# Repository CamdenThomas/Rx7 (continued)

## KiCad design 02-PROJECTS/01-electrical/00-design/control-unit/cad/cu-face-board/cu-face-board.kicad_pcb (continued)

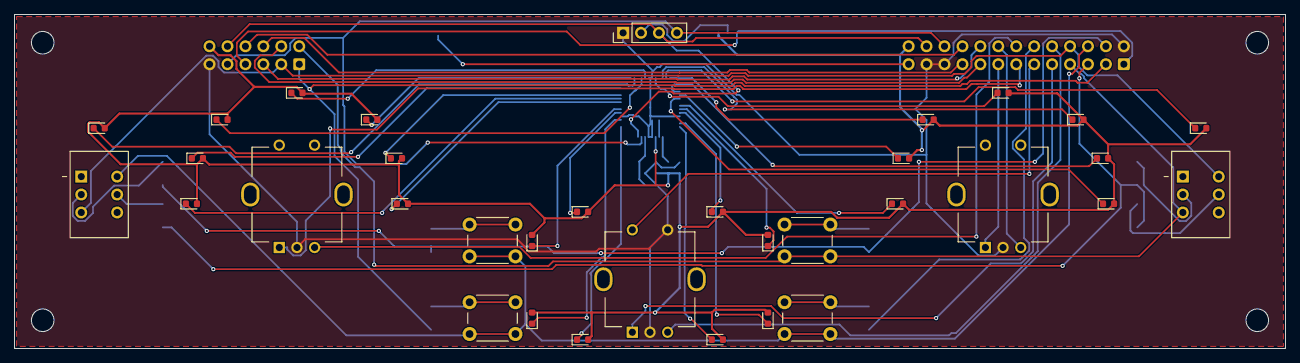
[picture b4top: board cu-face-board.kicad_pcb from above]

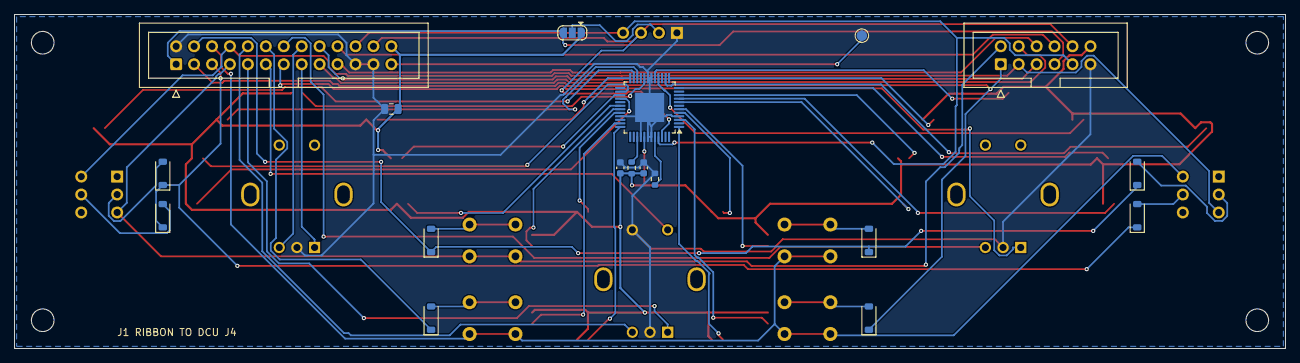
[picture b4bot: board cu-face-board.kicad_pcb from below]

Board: 2 copper layers, 180.0 x 47.3 mm, 56 parts (18 on the bottom side), 59 nets.

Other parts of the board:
H1, H2, H3, H4: M3; MountingHole_3.2mm_M3

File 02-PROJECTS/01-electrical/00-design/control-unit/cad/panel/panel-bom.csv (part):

"Ref","Qty","Value","Footprint","DNP","Confirm"
"C1","1","10uF 16V X7R","Capacitor_SMD:C_0805_2012Metric","","at J1 pin 26, for the LEDs' PWM current - part number confirm (P192)"
"C2","1","1uF","Capacitor_SMD:C_0603_1608Metric","","at U2 VCC - part number confirm (P192)"
"C3","1","100nF","Capacitor_SMD:C_0603_1608Metric","","at U2 VCC - part number confirm (P192)"
"D1-D8","8","1N4148W","Diode_SMD:D_SOD-123","",""
"J1","1","panel ribbon 2x13 IDC, keyed","Connector_IDC:IDC-Header_2x13_P2.54mm_Vertical","","keyed shrouded box header, the part bought confirm (P157); pin 1 toward the board's right edge"
"J2","1","screen module I2C 4-pin","Connector_PinHeader_2.54mm:PinHeader_1x04_P2.54mm_Vertical","","placeholder for the module's header (P201 not picked): pin order GND VCC SCL SDA and the standoff that brings the glass to the faceplate window - confirm"
"J3","1","plate header 2x6 IDC, keyed (DP-DCU-E 1-12)","Connector_IDC:IDC-Header_2x06_P2.54mm_Vertical","","the lead to the upper board's J8 (P196 class), pin n = DP-DCU-E n - confirm"
"LED1","1","key light rear defog","LED_SMD:LED_0603_1608Metric","","0603; colour per LP20 (P192), brightness on the bench - confirm. under the rear-defog cap (state, any time, I-004)"
"LED2","1","key light HVAC mode","LED_SMD:LED_0603_1608Metric","","0603; colour per LP20 (P192), brightness on the bench - confirm. under the fan-mode cap"
"LED3","1","key light recirculate","LED_SMD:LED_0603_1608Metric","","0603; colour per LP20 (P192), brightness on the bench - confirm. under the recirculate cap; green when on (I-001)"
"LED4","1","key light mirror defog","LED_SMD:LED_0603_1608Metric","","0603; colour per LP20 (P192), brightness on the bench - confirm. under the mirror-defog cap"
"LED5","1","knob ring 1","LED_SMD:LED_0603_1608Metric","","0603; colour per LP20 (P192), brightness on the bench - confirm. centre knob's ring, upper left (headlights only, I-004)"
"LED6","1","knob ring 2","LED_SMD:LED_0603_1608Metric","","0603; colour per LP20 (P192), brightness on the bench - confirm. centre knob's ring, upper right"
"LED7","1","knob ring 3","LED_SMD:LED_0603_1608Metric","","0603; colour per LP20 (P192), brightness on the bench - confirm. centre knob's ring, lower right"
"LED8","1","knob ring 4","LED_SMD:LED_0603_1608Metric","","0603; colour per LP20 (P192), brightness on the bench - confirm. centre knob's ring, lower left"
"LED9","1","window symbol DRV","LED_SMD:LED_0603_1608Metric","","0603; colour per LP20 (P192), brightness on the bench - confirm. beside the DRV window switch; a lit cap on the switch is a part question (I-005)"
"LED10","1","window symbol PASS","LED_SMD:LED_0603_1608Metric","","0603; colour per LP20 (P192), brightness on the bench - confirm. beside the PASS window switch (I-005)"
"LED11","1","seat symbol DRV","LED_SMD:LED_0603_1608Metric","","0603; colour per LP20 (P192), brightness on the bench - confirm. beside the driver seat knob: a fixed lit centre needs a hollow-shaft encoder, not chosen (I-005)"
"LED12","1","seat symbol PASS","LED_SMD:LED_0603_1608Metric","","0603; colour per LP20 (P192), brightness on the bench - confirm. beside the passenger seat knob (I-005)"
"LED13","1","driver seat cool 3","LED_SMD:LED_0603_1608Metric","","0603; colour per LP20 (P192), brightness on the bench - confirm. blue - driver seat arc, anticlockwise of OFF (D-073)"
"LED14","1","driver seat cool 2","LED_SMD:LED_0603_1608Metric","","0603; colour per LP20 (P192), brightness on the bench - confirm. blue"
"LED15","1","driver seat cool 1","LED_SMD:LED_0603_1608Metric","","0603; colour per LP20 (P192), brightness on the bench - confirm. blue"
"LED16","1","driver seat heat 1","LED_SMD:LED_0603_1608Metric","","0603; colour per LP20 (P192), brightness on the bench - confirm. red - clockwise of OFF"
"LED17","1","driver seat heat 2","LED_SMD:LED_0603_1608Metric","","0603; colour per LP20 (P192), brightness on the bench - confirm. red"
"LED18","1","driver seat heat 3","LED_SMD:LED_0603_1608Metric","","0603; colour per LP20 (P192), brightness on the bench - confirm. red"
"LED19","1","passenger seat cool 3","LED_SMD:LED_0603_1608Metric","","0603; colour per LP20 (P192), brightness on the bench - confirm. blue - passenger seat arc"
"LED20","1","passenger seat cool 2","LED_SMD:LED_0603_1608Metric","","0603; colour per LP20 (P192), brightness on the bench - confirm. blue"
"LED21","1","passenger seat cool 1","LED_SMD:LED_0603_1608Metric","","0603; colour per LP20 (P192), brightness on the bench - confirm. blue"
"LED22","1","passenger seat heat 1","LED_SMD:LED_0603_1608Metric","","0603; colour per LP20 (P192), brightness on the bench - confirm. red"
"LED23","1","passenger seat heat 2","LED_SMD:LED_0603_1608Metric","","0603; colour per LP20 (P192), brightness on the bench - confirm. red"
"LED24","1","passenger seat heat 3","LED_SMD:LED_0603_1608Metric","","0603; colour per LP20 (P192), brightness on the bench - confirm. red"
"R1","1","10k","Resistor_SMD:R_0603_1608Metric","","IMAX 7.6 mA per channel (p.11) - part number confirm (P192)"
"R2","1","100k","Resistor_SMD:R_0603_1608Metric","","SDB held high: on and blank until written - part number confirm (P192)"
"SW1","1","key - rear defog","Button_Switch_THT:SW_PUSH_6mm_H13mm","","Same Sky TS02-66-130-BK-160-LCR-D (P155, luxury D-488): 6 x 6 mm THT tactile, its top 13.0 mm above the board, 160 gf. The footprint is the maker's drawing rev 1.03: 6.5 x 4.5 mm, four 1.0 mm holes, pins 1-2 and 3-4 joined. The mock-up puts the cap's front 13 mm from the board (8 + 3 + 2): the cap's own top adds to that, or the 12.0 mm TS02-66-120-BK-160-LCR-D leaves it 1 mm - confirm with the cap (LP20)"
"SW2","1","key - HVAC mode","Button_Switch_THT:SW_PUSH_6mm_H13mm","","Same Sky TS02-66-130-BK-160-LCR-D (P155, luxury D-488): 6 x 6 mm THT tactile, its top 13.0 mm above the board, 160 gf. The footprint is the maker's drawing rev 1.03: 6.5 x 4.5 mm, four 1.0 mm holes, pins 1-2 and 3-4 joined. The mock-up puts the cap's front 13 mm from the board (8 + 3 + 2): the cap's own top adds to that, or the 12.0 mm TS02-66-120-BK-160-LCR-D leaves it 1 mm - confirm with the cap (LP20)"
"SW3","1","key - recirculate","Button_Switch_THT:SW_PUSH_6mm_H13mm","","Same Sky TS02-66-130-BK-160-LCR-D (P155, luxury D-488): 6 x 6 mm THT tactile, its top 13.0 mm above the board, 160 gf. The footprint is the maker's drawing rev 1.03: 6.5 x 4.5 mm, four 1.0 mm holes, pins 1-2 and 3-4 joined. The mock-up puts the cap's front 13 mm from the board (8 + 3 + 2): the cap's own top adds to that, or the 12.0 mm TS02-66-120-BK-160-LCR-D leaves it 1 mm - confirm with the cap (LP20)"
"SW4","1","key - mirror defog","Button_Switch_THT:SW_PUSH_6mm_H13mm","","Same Sky TS02-66-130-BK-160-LCR-D (P155, luxury D-488): 6 x 6 mm THT tactile, its top 13.0 mm above the board, 160 gf. The footprint is the maker's drawing rev 1.03: 6.5 x 4.5 mm, four 1.0 mm holes, pins 1-2 and 3-4 joined. The mock-up puts the cap's front 13 mm from the board (8 + 3 + 2): the cap's own top adds to that, or the 12.0 mm TS02-66-120-BK-160-LCR-D leaves it 1 mm - confirm with the cap (LP20)"
"SW5","1","window DRV","panel:Toggle_DPDT_SubMini_2x3_P2.54mm","","sub-miniature centre-sprung (ON)-OFF-(ON) DPDT toggle, 2 x 3 PC pins on 2.54 x 5.08 mm - part and pinout confirm (P155); lit cap for the window symbol is a part question (I-005)"
"SW6","1","window PASS","panel:Toggle_DPDT_SubMini_2x3_P2.54mm","","sub-miniature centre-sprung (ON)-OFF-(ON) DPDT toggle, 2 x 3 PC pins on 2.54 x 5.08 mm - part and pinout confirm (P155); lit cap for the window symbol is a part question (I-005)"
"SW7","1","encoder - centre","panel:RotaryEncoder_Bourns_Vertical_PEC11R-4xxxF-Sxxxx","","PEC11R-4220F-S0024 class (P155): detents, push, 20 mm shaft - confirm"
"SW8","1","encoder - driver seat","panel:RotaryEncoder_Bourns_Vertical_PEC11R-4xxxF-Sxxxx","","PEC11R-4220F-N0024 class (P155): detents, no push - confirm; the lit seat symbol in the knob's centre needs a hollow-shaft part (I-005), not chosen"
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
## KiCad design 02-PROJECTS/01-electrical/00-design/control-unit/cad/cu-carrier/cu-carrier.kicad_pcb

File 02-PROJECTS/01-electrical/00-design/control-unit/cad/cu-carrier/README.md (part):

# DCU carrier — the KiCad project

> **OUTDATED by the overhaul (D-612).** This is the last drawn state from before the boxes: the CU's connector is the DRC 64 with a DTP comfort inlet (D-594, D-612), the seats' heat and cool are its + side switches and the radar receiver is inside it (D-597), the face is the eighth pass (D-602), the CUR is on four I2C wires (D-604). It is kept as it is until row Y70 redraws it; the brief is `00-design/diagrams/overhaul-plan.html`, and the record (`../data/`) is what it must match.

*Rev 2026-10-13 (sheet rev 0.07 - Y44's fix pass, D-549, values only; rev 0.06 was Y44's one value, 0.05 Y42, 0.04 D-458, D-465, Y12) · owns: what this KiCad project
is for, what it may claim, and how to start. The board's design is `../../../../data/dcu_channels.csv`.
That is the record, and this is a drawing of it. Read `../../../README.md` first: it is the fence.*

> **Y49 / D-593 (2026-10-14): the dash-light stage is on the sheet, not yet on the board.** U17, a fifth BTS3011TE
> (IN from Teensy 11 through R73 100 R, R74 10 k to +3V3; STATUS on U13 P03 with R75 10 k; GND to PGND after the
> comfort shunt; OUT on `DASH_OUT`, class DRIVE, to TP2 until the header), and the wake request moved from Teensy 11
> to U13 P02. ERC 0; `check.py --board cu-carrier` 172 / 0. The board is rev 0.06 until Y54 places the stage beside the new
> header: its `--schematic-parity` DRC names exactly U17, R73-R75 and TP2 missing and J10 pad 13 / U13 pads 6-7 on
> their old nets. **Edit a copy of this whole folder** - a board saved by KiCad's Python without its .kicad_pro beside
> it gets default rules and writes them over this project's.

> **D-582 (2026-10-14): the connector edge changes.** The three DT13s (J1, J2, J9) give way to one CMC 48 header carrying every conductor the unit has, DP-DCU 1-48 - and the nets that went out on the upper board (J3, J5-J8, the dash-light stage) and the CUR's lines (the ribbon's plate nets) come to it too. Y54 draws that, once block 01.57 has picked the connector family; until then this board is as drawn, `check.py --board cu-carrier` still holds it to the old housings, and the scene hides J1 / J2 / J9.

## Where it stands

**2026-10-13 (Y44, D-549): sheet rev 0.07 - what the independent read found (D-548), values only.** No copper,
mask, silkscreen or drill changed: `fab/` was plotted again and every file is the same but its date, so the zip
is the one Y42 issued. ERC 0 / 0; DRC 0 violations, 0 unconnected, 0 parity; `check.py --board cu-carrier` 171 checks,
0 mismatches.

- **Q1 / Q2, the release selects, are Vishay SQ2364EES** (75975: 60 V, 0.245 ohm at 1.5 V on the gate, threshold
  0.46-1.0 V, gate +-8 V, SOT-23 G1 S2 D3). They are switched from Teensy pins at 3.3 V through 100 R with a 10 k
  pull-down, and the SQ2362CES named before has no on-resistance given under 4.5 V. D7 / D8 clamp the drains
  under 50 V.
- **Q4, the wake switch's driver, is MMBT5551** (160 V): its collector stands at the rail through R43, and the
  rail is clamped at 53 V. **D1, the logic input diode, is SL310A** (100 V 3 A, SMA), for the same reason.
- **C27, the DRV8962's charge-pump capacitor (CPH - CPL), is 100 nF 100 V**, the part on C25 / C30: TI's pin
  table (SLVSHN2A) asks 0.1 uF, VM-rated; 22 nF was drawn.
- **Not changed, to know at the bench:** a +3V3 track on the back passes 2.88 mm from H1's centre: **a nylon
  washer, or a nylon standoff, at H1**. The ribbon plug on J4 stands 4.9 mm in front of the Teensy's USB port:
  plug the USB lead in before the ribbon. GND and PGND meet only in the harness (D-382): with DP-DCU unplugged
  and DP-DCU-C live, the servo buck's input has no return but through the driver ICs' pins, so plug DP-DCU
  first and unplug it last. The DT13 pad numbering waits on the part in hand (D-548, V-117).

`fab/` also holds two hand-assembly drawings, `cu-carrier-revA-assembly-top.svg` and `-bottom.svg` (the back mirrored, to read
as you look at it): the outline, every part's outline and pads, and its reference in the middle of the part; the
values are in `control-unit/data/cu-carrier-revA-bom.csv` by reference. `00-design/tools/assembly.py` rebuilds them (KiCad's Python);
`00-design/tools/fabpack.py` re-plots the gerbers and drill files and writes the zip.

**2026-10-13 (Y42): rev 0.05 - what pricing the order found, made right before the boards are ordered (D-541).**
`fab/` is bench revision A re-issued from this board: the zip keeps its name, and the rev 0.04 package must not be
ordered. ERC 0 / 0; DRC 0 violations, 0 unconnected, 0 parity; `check.py --board cu-carrier` 171 checks, 0 mismatches.

- **Q3, the wake switch, was drawn gate / drain / source on a SOT-23.** Every SOT-23 P-FET is gate 1, source 2,
  drain 3 (Vishay 66894, top view), so the part would have sat drain to `+12V_LOGIC` and source to `WAKE_OUT`:
  its body diode holds the wake line at 12 V and the car never sleeps. The symbol is `Q_PMOS_GSD` now, pad 2 is
  `+12V_LOGIC` and pad 3 `WAKE_OUT`; the two short runs at its pads were re-laid and the `WAKE_OUT` via moved
  1.9 mm, to (152.15, 44.75). The part is **SQ2361ES** (60 V): its source sits on a rail the SMBJ33A clamps at
  53.3 V, so D-273's rule asks 60 V, and the SQ2351ES the sheet named is a 20 V part.
- **D2, D4 (SMBJ33A) and D7, D8 (SMAJ40A) are one-way parts and were drawn with two anodes**, pad 1 - the end
  the silkscreen marks as the cathode - on ground. Fitted to the mark they conduct forward: D2 / D4 short their
  inputs, D7 / D8 hold the hatch and fuel-door relays on. The symbol is `D_TVS_Uni` (pin 1 the cathode) and each
  footprint is turned half a turn in place: the same copper, the mark at the rail or drain end.
- **C1, C8, C29 are 68 µF 63 V** (Panasonic EEE-FK1J680UP), not 100 µF. Each sits across an SMBJ33A, so the same
  rule asks more than 53.3 V and a 50 V part is out; in the FK series 100 µF 63 V is a 10 × 10.2 can (size G, lands
  4.1 × 2.0 with 4.6 between) and the footprint drawn is the 8 × 10.2 one (size F), whose largest 63 V value is
  68 µF. The record names no value for this capacitor (`dcu_channels` gives the buck's ceramics), so the value
  moved and the board did not; 100 µF needs the 10 mm footprint and room it does not have here without a re-lay.
- **Values that follow the cart**: C31-C33 470 µF 16 V (the same can as 10 V); Q1 / Q2 were SQ2362CES or PMV37ENEA
  here (Nexperia lists PMV37ENEA in production, but four distributors had none) and are SQ2364EES since rev 0.07,
  above.
- **Q3's gate divider (Y44, sheet rev 0.06, a value only): R43 is 18 k, was 1 k** (R42, gate to source, stays
  10 k). With 1 k the gate saw ten elevenths of the rail while the wake is asserted, past the part's ±20 V once
  the rail passed 22 V. Now it sees 10 / 28: 3.2 V at 9 V, 4.3 at 12, 5.1 at 14.4, 8.6 at 24 and 19.0 V at the
  SMBJ33A's 53.3 V clamp. Q3 carries milliamps (a diode into the wake strip's bleed resistor), and Vishay 66894
  gives a threshold of 2.5 V at most and about 0.6 A at 3 V, so 3.2 V is on for that load. No copper, mask,
  silkscreen or drill changed: `fab/` was re-plotted and compared, every file the same but its date.

These four boards have no generator (only the left plate does): the change was made by two scripts on the sheet and
the board themselves - nodes replaced in the `.kicad_sch` / `.kicad_sym`, the board through KiCad's `pcbnew`.

**2026-10-12 (Y17): bench revision A (board rev 0.04) is packaged under `fab/`** - gerbers, Excellon drill
(PTH / NPTH, maps), `cu-carrier-revA-gerbers.zip` and `cu-carrier-revA-bom.csv` (MPNs `confirm` where the sheet
does not name them; the D-489 / D-455 parts listed as not fitted), from this board on its provisional outline, for
the bench order of D-490; the final board follows F11.

**2026-10-12 (Y20, D-492): J4's pins 9-12 carry the new names** - `ENC_FAN_A` / `ENC_FAN_B` → `ENC_CENTRE_A` / `ENC_CENTRE_B`, `ENC_TEMP_A` → `ENC_CENTRE_PUSH`, `ENC_TEMP_B` → `ROW4` - on the sheet's labels and the Teensy symbol's pin names, and the board's nets renamed to match (no footprint or copper moved; the same Teensy pins 40 / 41 / 34 / 35). ERC 0, DRC 0 / 0 with 0 parity issues, `00-design/tools/check.py --board cu-carrier` 0 mismatches. The `fab/` package still carries the old names in its netlist attributes; the copper is the same.

**Sheet and board are both rev 0.04 (Y12, 2026-10-11).** The sheet carries D-458 and D-465; ERC is 0 / 0 and
`00-design/tools/check.py --board cu-carrier` reads 0 mismatches:

- **J4 is a 2 x 13 keyed IDC header** (26-way, D-458). Pins 1-20 keep their nets. 21 and 23 are
  `GND`. 22 `PNL_SDA` and 24 `PNL_SCL` are the I²C bus (Teensy 18 / 19, the bus of U12, U13 and U15)
  through **R71 / R72, 100 Ω** series resistors. 25 `SPARE` ends on the test pad **TP1**. 26
  `+5V_PNL` is the logic `+5V` through **F1, a 0.5 A-hold PTC** (1206L050 class, `confirm`), so a
  short on the panel trips F1 and never browns out the Teensy. No BAT54S clamp: there is no room for
  one by J4. The panel's driver has 8 kV HBM on its pins, the Teensy has its own clamps, and the
  100 Ω limits the current into both (`confirm`). The panel bus runs at 100 kHz (`confirm`).
- **R39 / R41, the K3 / K4 select gate pull-downs, are 10 kΩ** (were 100 kΩ, D-465). Each sits gate
  to source behind its 100 Ω series resistor, so a floating Teensy pin cannot fire a release: an empty
  socket, reset, boot or an unprogrammed part. The 10 kΩ also holds the gate against drain-gate
  coupling when the relay coil switches. A driven pin pays 0.33 mA for it.

**The top-left block was re-laid for the 2 x 13 header (Y12).** Its courtyard (41.8 mm) is 1.9 mm longer
than the gap the 2 x 10 had between H1's screw head and the Teensy's USB end, so:

- **J4 sits three pitches (7.62 mm) further left**, pin 1 at (6.38, 7.6): pins 7-26 stand on the 2 x 10's
  pads 1-20, and the header's right end, with the 13 mm the bus needs to reach the Teensy, is where it
  was. The Teensy socket J10 did not move.
- **H1 moved to (4, 15)**, under the header's left end (the other three holes stay 4 mm from their
  corners). `confirm` with `V-102` / `CK26`.
- **F1, R72, R71 stand in the gap between the header and the Teensy**, by pins 21-26: F1 with pad 1 on the
  +5V track and pad 2 straight to pin 26; R72 beside the I²C clock's via; R71 astride the +3V3 trunk with
  pad 1 on the SDA trunk. **TP1** is on the bottom side beside pin 25.
- The six 0805s H1 landed on moved: R52 / R54 between H1 and U12, R53 / R3 / C24 below H1, R51 onto
  the SDA trunk above U12.

An earlier placement (pin 1 3.0 mm left, the new parts in the old H1 corner) left four nets open: its
three extra columns stood in the bus's way to the Teensy, and +5V lost its way round the header.

**D-479 (2026-10-11): this board now lives inside the Control Unit**, one enclosure with the
control panel's board on its face, like a stereo head unit, with only sealed connector halves outside.
The panel ribbon (J4) stays inside the box, and nothing leaves through a grommet: the servo leads
(J6-J8), the blower duty (J5) and the cabin sensor (J3) go out on a sealed half of their own. The
connector edge is full (160.5 of 165 mm), so that half, `DP-DCU-D`, is a fourth DT13-12PA in a second
row above J9, on a small upper connector board joined to J6-J8, J5 and J3 by short plug-in leads
(D-480, parts P194-P196). **This board does not change for it.** The unit's mock-up is `../cu-assembly/`
(`Y14`), the upper board's drawing is `Y15`. The Y7 box in `enclosure/` is the old DCU-only box, kept
until the unit's enclosure replaces it.

**The board is laid out, routed and 3D-modelled on a PROVISIONAL outline (Y5), with the open blocks'
worst case drawn in (Y11, D-455) and the 26-way header (Y12).** `kicad-cli pcb drc --severity-all
--exit-code-violations --schematic-parity` reads 0 violations (errors and warnings), 0 unconnected,
0 parity issues; ERC is 0 / 0. `00-design/tools/check.py --board cu-carrier` holds every record pin; its one remaining line
is a note on DP-DCU-B 12, wired here to the clutch stage for block 02.15 behind a sealing plug. `H-002`
stays the final board: it gates on `V-102`, luxury `W-332` and this row. Nothing here is ordered (F5).

- **The sheet** (since rev 0.03): every functional block is on its real package, its pin numbers held to
  `00-design/tools/pin_tables.csv` by `check.py` (S-480 to S-489):
  - U5-U8 **BTS3011TE**, TO-252-5: 1 IN, 2 VDD, 3 OUT, 4 STATUS, 5 GND (the source - the seat
    current leaves here), tab 6 = OUT. **STATUS** is open-drain and latching on an over-temperature
    shutdown (datasheet section 7.1, p.20): the four are wired-OR on `SEAT_STATUS`, pulled up by R58
    10 k to `+3V3` (the R_STATUS of the application table, p.40) and read on the second expander
    **U13 P00** (Y11; U12 P17 went back to the A/C clutch). The
    latch clears with IN low and STATUS high, so firmware drops all four inputs to clear it; which
    switch tripped is not told apart. `confirm`.
  - U9 **BTT6050-1ERA**, PG-TSDSO-14: 3 GND (47 Ω PROFET ground), 4 IN, 5 DEN, 6 IS, 10-12 OUT, tab VS
    on `+12V_CMF`.
  - U10 **BTT6200-4ESA**, PG-TSDSO-24: 2 IN0, 4 GND, 5 IN1, 6 DEN, 7 IS, 8 DSEL0, 9 IN2, 10 IN3,
    11 DSEL1, 13 OUT3, 17 OUT2, 20 OUT1, 24 OUT0, tab VS on `+12V_LOGIC`; DEN / DSEL0 / DSEL1 on
    expander P11-P13 (SN22).
  - U11 **DRV8962-Q1**, HTSSOP-44 (SLVSHN2A): every pin. The three pins of each OUT paralleled, VM on
    2 / 11 / 12 / 21, PGND1-4 and GND to the exposed pad, IPROPI1-4 each to its own 1.5 k (`confirm`
    against the stall current, W-332), **VCC tied to DVDD** (p.4: "when separate logic supply voltage
    is not available, tie the VCC pin to the DVDD pin"), VREF on `+3V3`. **MODE to GND**: on this part MODE is not a control
    mode but the output slew rate, low = 140 ns rise / fall, the quieter one (p.4, p.7, section 6.4
    p.12); the part always runs as four independent half-bridges, EN/IN per channel, as SN17 wants.
    **OCPM to GND = latch-off** (section 6.10.4, p.19): a stalled mirror motor latches the driver off
    until an nSLEEP reset pulse, which the firmware gives through the expander (P07). `confirm`.
  - U2 TPS54560B-Q1 (DDA), U4 INA180A1 and U12 TCA9539-Q1 were already on their real pins.
- **The provisions** (Y11, the `PROVISIONS` box; D-455: the worst case of each open block, so an answer
  is a fitting change, not a redesign). Every part is **DNP** with its block and reason in its `Note`
  field, except U13 and C38:
  - **U13** TCA9539-Q1 at **0x75** (A0 high, A1 low), fitted: P00 `SEAT_STATUS`, P01 the radar alert,
    P02-P17 spare. Same I²C bus as U12 (R51 / R52), INT wired-OR on `EXP_INT` (R53, Teensy 12), RESET
    shared on `EXP_RESET` (R54): a reset holds both expanders' ports as inputs.
  - **A/C clutch** (engine 02.15 (b)): U12 **P17** `AC_CLUTCH_CMD` → R59 4.7 k (R60 10 k off at reset) →
    **U14 BTT6050-1ERA** high side, VS on `V12C_RAW` (the comfort input ahead of D3, so a ~4 A coil never
    passes the B560C), OUT `AC_CLUTCH` on **DP-DCU-B 12** (the one free cavity of the three receptacles).
    DEN low (R61), IS on R62 1.2 k unread, 47 Ω ground (R63) - as U9. The coil returns at the compressor
    and must carry its own diode (EAS 60 mJ); F29 (7.5 A) needs 10 A with it - `confirm` (V-101).
  - **A/C pressure** (02.15 (b)): **J11** a 3-way PLACEHOLDER lead (no drop cavity is free for its three
    wires), 0.5-4.5 V ratiometric `confirm`, 10 k / 20 k + 100 nF + BAT54S → **U15 ADS1115-Q1** (0x48,
    VSSOP-10) AIN0; the sensor supply the same way on AIN2; AIN1 / AIN3 grounded, spare. **U16
    TPS7B4250-Q1** makes `SENS_5V` from logic 12 V, tracking `+5V` and proof against a short to battery.
  - **Radar alert** (luxury 03.12 / Z-002): **J12** a 2-way PLACEHOLDER lead → 47 k / 22 k + 100 nF +
    BAT54S → U13 P01; R68 10 k to logic 12 V only for an open-collector output (`confirm`).
  - **DP-DCU-C 8** (J2 pin 8) on `PGND`: 01.26 (a)'s third comfort ground. The record keeps the cavity a
    sealing plug until 01.26 answers; the copper is there either way.
- **CONVENTIONS §5 holds**: `+12V_LOGIC` and `+12V_CMF` share no part, and only U4 touches both `GND`
  and `PGND`. On the board the two grounds share no copper either.

**R11 applies to all of it:** nothing on this board has been measured. The outline is a guess, the DT13
hole pattern is TE's drawing, the Teensy socket is PJRC's card, and the mirror stage's values wait on
luxury `W-332`.

## The board

**Outline: 180 x 80 mm, PROVISIONAL - `confirm` until `V-102` (D-455).** The brief's 120 x 80 does
not hold the three flanged DT13s side by side on one edge: their courtyards (flange ears included) are
60.3 + 56.1 + 44.1 mm, so the connector edge needs about 165 mm. Four M3 holes (3.2 mm, NPTH): H2-H4
4 mm in from their corners, H1 at (4, 15) below the ribbon header (Y12). 2 layers, 1.6 mm, 1 oz.

- **The connector edge** is the bottom long edge: J9 `DP-DCU-B` DT13-12PA (left, x 38.1), J2
  `DP-DCU-C` DT13-08PA (centre, x 97.2), J1 `DP-DCU` DT13-06PA (right, x 148.2). The board edge sits on
  each flange's rear face (4 mm behind its front face), flush for panel mounting through one enclosure
  wall (D-362).
- **The opposite edge** (grommets, D-362): J4 the panel ribbon (2 x 13 IDC, D-458; in the top left
  corner, pin 1 at (6.38, 7.6), its courtyard from 0.7 to 42.5 mm along the edge), the Teensy (J10,
  socketed, along the top, pad 1 at (50, 18), its courtyard from 47.4 mm), the three servo headers J6-J8
  each with its 470 µF beside it, J3 the cabin NTC lead and J5 the blower pigtail (top right).
- **Blocks**: the window quad U10 and the mirror bridge U11 over J9 (their outputs face the pins), the
  releases Q1 / Q2 beside them, the mirror heat U9 between J9 and J2; the four seat switches U5-U8 over
  J2, tabs down onto their pins; the shunt R15 / R16 and U4 to their right; the logic buck U1 and the
  servo buck U2 top right, under the servo headers they feed; CAN U3, the wake stage and the
  outside-air input over J1; the expander U12 top left below the ribbon, with the panel lines' F1 / R72 /
  R71 at the header's right end and TP1 under it (Y12).
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
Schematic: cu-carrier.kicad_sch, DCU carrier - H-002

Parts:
C1, C8, C29: 68u 63V; CP_Elec_8x10
C2, C9, C10: 4.7u 100V X7R; C_1210_3225Metric
C3: 220n 100V; C_0805_2012Metric
C4, C11: 100n 16V; C_0805_2012Metric
C5: 1u 16V; C_0805_2012Metric
C6: 20p C0G; C_0805_2012Metric
C7: 22u 16V X7R; C_1206_3216Metric
C12: 4.7n confirm; C_0805_2012Metric
C13: 47p confirm; C_0805_2012Metric
C14, C15: 47u 10V X7R; C_1210_3225Metric
C16, C17, C18, C19, C20, C21, C22, C23, C24, C34: 100n; C_0805_2012Metric
C25, C27, C30: 100n 100V; C_0805_2012Metric
C26: 1u 25V confirm; C_0805_2012Metric
C28: 1u; C_0805_2012Metric
C31, C32, C33: 470u 16V; CP_Elec_8x10
C35: 100n at pin 25 (VCC); C_0805_2012Metric
C36: 10n 100V VM-PGND1 (TI 6-1); C_0805_2012Metric
C37: 10n 100V VM-PGND3 (TI 6-1); C_0805_2012Metric
C38: 100n U13 VCC; C_0805_2012Metric
C39: 100n U15 VDD; C_0805_2012Metric; not fitted
C40: 1u 50V; C_0805_2012Metric; not fitted
C41, C43, C44, C45: 100n; C_0805_2012Metric; not fitted
C42: 2.2u; C_0805_2012Metric; not fitted
D1: SL310A; D_SMA
D2, D4: SMBJ33A; D_SMB
D3: B560C 60V 5A - confirm; D_SMC
D5: B560C 60V 5A catch; D_SMC
D6: BAT54S; SOT-23
D7, D8: SMAJ40A confirm; D_SMA
D9, D10, D11: BAT54S; SOT-23; not fitted
F1: PTC 0.5A hold 1206 - confirm; Fuse_1206_3216Metric
J1: DP-DCU DT13-06PA; DT13-06PA
J2: DP-DCU-C DT13-08PA; DT13-08PA
J3: cabin NTC lead; JST_XH_B2B-XH-A_1x02_P2.50mm_Vertical
J4: panel ribbon 2x13 IDC, keyed; IDC-Header_2x13_P2.54mm_Vertical
J5: blower pigtail; JST_XH_B2B-XH-A_1x02_P2.50mm_Vertical
J6, J7, J8: servo header; PinHeader_1x03_P2.54mm_Vertical
J9: DP-DCU-B DT13-12PA; DT13-12PA
J10: Teensy 4.1 socket - 2 x 24 female headers; Teensy41_Socket
J11: A/C pressure transducer lead - PLACEHOLDER; JST_XH_B3B-XH-A_1x03_P2.50mm_Vertical; not fitted
J12: radar alert lead - PLACEHOLDER; JST_XH_B2B-XH-A_1x02_P2.50mm_Vertical; not fitted
L1: 2.2u XAL4020-222; L_Coilcraft_XAL4020-XXX
L2: 6.8u Isat >= 7 A - confirm; L_Coilcraft_XAL7030-682
L3: common-mode choke - DNP, fit only with R instead 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; L_CommonModeChoke_Coilank_ACM2012; not fitted
Q1, Q2: SQ2364EES; SOT-23
Q3: SQ2361ES; SOT-23
Q4: MMBT5551; SOT-23
R1: 100k 1%; R_0805_2012Metric
R2: 24.9k 1%; R_0805_2012Metric
R3, R45: 100k; R_0805_2012Metric
R4: 243k 1% ~400 kHz; R_0805_2012Metric
R5: 52.3k 1%; R_0805_2012Metric
R6, R11, R13: 10k 1%; R_0805_2012Metric
R7: 16.9k confirm; R_0805_2012Metric
R8, R12, R14, R36, R39, R41, R42, R44, R53: 10k; R_0805_2012Metric
R9, R10: 0R fitted in place of the choke; R_0805_2012Metric
R15, R16: 10m 2512 3W; R_2512_6332Metric
R17, R18, R19, R20, R22: 10k off at reset; R_0805_2012Metric
R21, R23, R26, R27, R28, R29, R30, R31, R32, R51, R52: 4.7k; R_0805_2012Metric
R24: 1.2k IS unread - no ADC pin left; R_0805_2012Metric
R25, R34: 47R PROFET ground; R_0805_2012Metric
R33: 1.2k IS unread; R_0805_2012Metric
R35: 100k asleep at reset; R_0805_2012Metric
R37, R55, R56, R57: 1.5k confirm vs stall (W-332); R_0805_2012Metric
R38, R40, R46, R71, R72: 100R; R_0805_2012Metric
R43: 18k; R_0805_2012Metric
R47: 10k off through a reset; R_0805_2012Metric
R48, R49, R50: 330R; R_0805_2012Metric
R54: 10k held in reset until the firmware lets go; R_0805_2012Metric
R58: 10k STATUS pull-up (BTS3011TE p.40); R_0805_2012Metric
R59: 4.7k; R_0805_2012Metric; not fitted
R60: 10k off at reset; R_0805_2012Metric; not fitted
R61: 4.7k DEN low; R_0805_2012Metric; not fitted
R62: 1.2k IS unread; R_0805_2012Metric; not fitted
R63: 47R PROFET ground; R_0805_2012Metric; not fitted
R64, R66, R68: 10k; R_0805_2012Metric; not fitted
R65, R67: 20k; R_0805_2012Metric; not fitted
R69: 47k; R_0805_2012Metric; not fitted
R70: 22k; R_0805_2012Metric; not fitted
R73: 100 dash IN series (SN31); R_0805_2012Metric
R74: 10k dash IN pull-up: full at reset (SN31); R_0805_2012Metric
R75: 10k dash STATUS pull-up (BTS3011TE p.40); R_0805_2012Metric
TP1: ribbon spare; TestPoint_Pad_D1.0mm
TP2: DASH_OUT - to DP-DCU 35 at Y54; TestPoint_Pad_2.5x2.5mm
U1: LMR36015FSCQ-Q1; Texas_RNX0012C_VQFN-14-11-1EP_2x3mm_P0.5mm_EP0.25x1.825mm
U2: TPS54560B-Q1; HSOP-8-1EP_3.9x4.9mm_P1.27mm_EP2.41x3.1mm
U3: TCAN1042HVDRQ1; SOIC-8_3.9x4.9mm_P1.27mm
U4: INA180A1; SOT-23-5
U5, U6, U7, U8, U17: BTS3011TE; TO-252-5_TabPin6
U9: BTT6050-1ERA; Infineon_PG-TSDSO-14-22
U10: BTT6200-4ESA; Infineon_PG-TSDSO-24-21
U11: DRV8962-Q1; HTSSOP-44-1EP_6.1x14mm_P0.635mm_EP5.2x14mm_Mask4.31x8.26mm
U12, U13: TCA9539-Q1; TSSOP-24_4.4x7.8mm_P0.65mm
U14: BTT6050-1ERA; Infineon_PG-TSDSO-14-22; not fitted
U15: ADS1115-Q1; MSOP-10_3x3mm_P0.5mm; not fitted
U16: TPS7B4250-Q1; SOT-23-5; not fitted

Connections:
+3V3: C17.1, C20.1, C21.1, C22.1, C23.1, C24.1, C34.1, C38.1, C39.1, D6.2 (K), D9.2 (K), D10.2 (K), D11.2 (K), J4.1, J10.15 (3V3), J10.46 (3V3), R3.1, R11.1, R13.1, R36.1, R51.1, R52.1, R53.1, R58.1, R74.2, R75.2, U3.5 (VIO), U4.5 (VS), U5.2 (VDD), U6.2 (VDD), U7.2 (VDD), U8.2 (VDD), U11.33 (VREF), U12.24 (VCC), U13.21 (A0), U13.24 (VCC), U15.8 (VDD), U17.2 (VDD)
+5V: C6.1, C7.1, C16.1, C41.1, F1.1, J10.48 (VIN), L1.2, R1.1, U3.3 (VCC), U16.1 (ADJ/EN)
+5V_SERVO: C14.1, C15.1, C31.1, C32.1, C33.1, J6.2, J7.2, J8.2, L2.2, R5.1
+12V_CMF: C8.1, C9.1, C10.1, D3.1 (K), D4.1 (K), U2.2 (VIN), U9.TAB (VS)
+12V_LOGIC: C1.1, C2.1, C3.1, C25.1, C26.2, C29.1, C30.1, C36.1, C37.1, C40.1, D1.1 (K), D2.1 (K), Q3.2 (S), R42.1, R68.1, U1.2 (VIN), U1.9 (EN), U1.10 (VIN), U10.TAB (VS), U11.2 (VM), U11.11 (VM), U11.12 (VM), U11.21 (VM), U16.3 (VIN)
/+5V_PNL: F1.2, J4.26
/AC_CLUTCH: J9.12, U14.10 (OUT), U14.11 (OUT), U14.12 (OUT)
/AC_CLUTCH_CMD: R59.1, R60.1, U12.20 (P17)
/AC_DEN_R: R61.1, U14.5 (DEN)
/AC_GND: R63.1, U14.3 (GND)
/AC_IN: R59.2, U14.4 (IN)
/AC_IS: R62.1, U14.6 (IS)
/AC_PRESS_ADC: C43.1, D9.3 (COM), R64.2, R65.1, U15.4 (AIN0)
/AC_PRESS_IN: J11.2, R64.1
/BLOWER_PWM: J5.1, R46.2
/BLOWER_T: J10.12 (10 BLOWER_T), R46.1, R47.1
/BUCK_BOOT: C4.1, U1.4 (BOOT)
/BUCK_FB: C6.2, R1.2, R2.1, U1.7 (FB)
/BUCK_SW: C4.2, L1.1, U1.3 (NC), U1.12 (SW)
/BUCK_VCC: C5.1, U1.5 (VCC)
/CABIN_ADC: C18.1, J10.36 (14 CABIN_ADC), R12.2
/CANH_J: J1.4, L3.2, R9.2
/CANH_U: L3.1, R9.1, U3.7 (CANH)
/CANL_J: J1.5, L3.4, R10.2
/CANL_U: L3.3, R10.1, U3.6 (CANL)
/CAN_RXD: J10.2 (0 CAN_RXD), U3.4 (RXD)
/CAN_STB: R8.1, U3.8 (STB), U12.18 (P15)
/CAN_TXD: J10.3 (1 CAN_TXD), U3.1 (TXD)
/CMF_RTN: R15.1, R16.1, U4.3 (IN+), U5.5 (GND), U6.5 (GND), U7.5 (GND), U8.5 (GND)
/COL1: J4.6, J10.23 (31 COL1)
/COL2: J4.7, J10.24 (32 COL2)
/COL3: J4.8, J10.25 (33 COL3)
/CUR_ADC: J10.38 (16 CUR_ADC), U4.1 (OUT)
/ENC_CENTRE_A: J4.9, J10.32 (40 ENC_CENTRE_A)
/ENC_CENTRE_B: J4.10, J10.33 (41 ENC_CENTRE_B)
/ENC_CENTRE_PUSH: J4.11, J10.26 (34 ENC_CENTRE_PUSH)
/ENC_SEAT_DRV_A: J4.13, J10.28 (36 ENC_SEAT_DRV_A)
/ENC_SEAT_DRV_B: J4.14, J10.29 (37 ENC_SEAT_DRV_B)
/ENC_SEAT_PASS_A: J4.15, J10.30 (38 ENC_SEAT_PASS_A)
/ENC_SEAT_PASS_B: J4.16, J10.31 (39 ENC_SEAT_PASS_B)
/EXP_INT: J10.14 (12 EXP_INT), R53.2, U12.1 (INT), U13.1 (INT)
/EXP_RESET: J10.35 (13 EXP_RESET), R54.1, U12.3 (RESET), U13.3 (RESET)
/I2C_SCL: J10.41 (19 I2C_SCL), R52.2, R72.1, U12.22 (SCL), U13.22 (SCL), U15.10 (SCL)
/I2C_SDA: J10.40 (18 I2C_SDA), R51.2, R71.1, U12.23 (SDA), U13.23 (SDA), U15.9 (SDA)
/JOY_PRESS: J4.19, J10.39 (17 JOY_PRESS)
/JOY_X: J4.17, J10.42 (20 JOY_X)
/JOY_Y: J4.18, J10.43 (21 JOY_Y)
/MH_DEN: R23.1, U12.17 (P14)
/MH_DEN_R: R23.2, U9.5 (DEN)
/MH_GND: R25.1, U9.3 (GND)
/MH_IN: R21.2, U9.4 (IN)
/MH_IN_T: J10.11 (9 MH_IN_T), R21.1, R22.1
/MH_IS: R24.1, U9.6 (IS)
/MIRROR_HEAT: J9.9, U9.10 (OUT), U9.11 (OUT), U9.12 (OUT)
/MIR_CLUTCH: J9.8, U11.14 (OUT4), U11.15 (OUT4), U11.16 (OUT4)
/MIR_COM: J9.5, U11.4 (OUT1), U11.5 (OUT1), U11.6 (OUT1)
/MIR_CPH: C27.1, U11.44 (CPH)
/MIR_CPL: C27.2, U11.43 (CPL)
/MIR_DVDD: C28.1, C35.1, U11.24 (DVDD), U11.25 (VCC)
/MIR_EN1: U11.37 (EN1), U12.5 (P01)
/MIR_EN2: U11.36 (EN2), U12.7 (P03)
/MIR_EN3: U11.35 (EN3), U12.9 (P05)
/MIR_EN4: U11.34 (EN4), U12.10 (P06)
/MIR_IN1: U11.41 (IN1), U12.4 (P00)
/MIR_IN2: U11.40 (IN2), U12.6 (P02)
/MIR_IN3: U11.39 (IN3), U12.8 (P04)
/MIR_IPROPI1: R37.1, U11.32 (IPROPI1)
/MIR_IPROPI2: R55.1, U11.31 (IPROPI2)
/MIR_IPROPI3: R56.1, U11.30 (IPROPI3)
/MIR_IPROPI4: R57.1, U11.29 (IPROPI4)
/MIR_L: J9.6, U11.7 (OUT2), U11.8 (OUT2), U11.9 (OUT2)
/MIR_R: J9.7, U11.17 (OUT3), U11.18 (OUT3), U11.19 (OUT3)
/MIR_VCP: C26.1, U11.1 (VCP)
/MIR_nFAULT: R36.2, U11.26 (nFAULT), U12.13 (P10)
/MIR_nSLEEP: R35.1, U11.42 (nSLEEP), U12.11 (P07)
/NTC_CABIN: J3.1, R11.2, R12.1
/OAT_ADC: C19.1, D6.3 (COM), J10.37 (15 OAT_ADC), R14.2
/OAT_IN: J1.2, R13.2, R14.1
/PG_5V: R3.2, U1.8 (PG), U12.19 (P16)
/PNL_SCL: J4.24, R72.2
/PNL_SDA: J4.22, R71.2
/RADAR_ALERT: C45.1, D11.3 (COM), R69.2, R70.1, U13.5 (P01)
/RADAR_IN: J12.1, R68.2, R69.1
/REL_FUEL: D8.1 (K), J9.11, Q2.3 (D)
/REL_FUEL_G: Q2.1 (G), R40.2, R41.1
/REL_FUEL_T: J10.19 (27 REL_FUEL_T), R40.1
/REL_HATCH: D7.1 (K), J9.10, Q1.3 (D)
/REL_HATCH_G: Q1.1 (G), R38.2, R39.1
/REL_HATCH_T: J10.18 (26 REL_HATCH_T), R38.1
/ROW1: J4.3, J10.20 (28 ROW1)
/ROW2: J4.4, J10.21 (29 ROW2)
/ROW3: J4.5, J10.22 (30 ROW3)
/ROW4: J4.12, J10.27 (35 ROW4)
/SC_DRV_IN: J10.9 (7 SC_DRV_IN), R19.1, U7.1 (IN)
/SC_DRV_RTN: J2.3, U7.3 (OUT), U7.6 (OUT)
/SC_PASS_IN: J10.10 (8 SC_PASS_IN), R20.1, U8.1 (IN)
/SC_PASS_RTN: J2.4, U8.3 (OUT), U8.6 (OUT)
/SEAT_STATUS: R58.2, U5.4 (STATUS), U6.4 (STATUS), U7.4 (STATUS), U8.4 (STATUS), U13.4 (P00)
/SENS_5V: C42.1, J11.1, R66.1, U16.4 (VOUT)
/SENS_5V_ADC: C44.1, D10.3 (COM), R66.2, R67.1, U15.6 (AIN2)
/SH_DRV_IN: J10.7 (5 SH_DRV_IN), R17.1, U5.1 (IN)
/SH_DRV_RTN: J2.1, U5.3 (OUT), U5.6 (OUT)
/SH_PASS_IN: J10.8 (6 SH_PASS_IN), R18.1, U6.1 (IN)
/SH_PASS_RTN: J2.2, U6.3 (OUT), U6.6 (OUT)
/SPARE: J4.25, TP1.1
/SRV_BLEND: J7.1, R49.2
/SRV_BLEND_T: J10.5 (3 SRV_BLEND_T), R49.1
/SRV_BOOT: C11.1, U2.1 (BOOT)
/SRV_CC: C12.1, R7.2
/SRV_COMP: C13.1, R7.1, U2.6 (COMP)
/SRV_FB: R5.2, R6.1, U2.5 (FB)
/SRV_MODE: J6.1, R48.2
/SRV_MODE_T: J10.4 (2 SRV_MODE_T), R48.1
/SRV_RECIRC: J8.1, R50.2
/SRV_RECIRC_T: J10.6 (4 SRV_RECIRC_T), R50.1
/SRV_RT: R4.1, U2.4 (RT/CLK)
/SRV_SW: C11.2, D5.1 (K), L2.1, U2.8 (SW)
/V12C_RAW: D3.2 (A), J2.5, U14.TAB (VS)
/V12L_RAW: D1.2 (A), J1.1
/WAKE_B: Q4.1 (B), R44.2
/WAKE_C: Q4.3 (C), R43.2
/WAKE_G: Q3.1 (G), R42.2, R43.1
/WAKE_OUT: J1.6, Q3.3 (D)
/WIN_DEN: R30.1, U12.14 (P11)
/WIN_DEN_R: R30.2, U10.6 (DEN)
/WIN_DRV_DN: J9.2, U10.20 (OUT1)
/WIN_DRV_UP: J9.1, U10.24 (OUT0)
/WIN_DSEL0: R31.1, U12.15 (P12)
/WIN_DSEL0_R: R31.2, U10.8 (DSEL0)
/WIN_DSEL1: R32.1, U12.16 (P13)
/WIN_DSEL1_R: R32.2, U10.11 (DSEL1)
/WIN_GND: R34.1, U10.4 (GND)
/WIN_IN0: J10.44 (22 WIN_IN0), R26.1
/WIN_IN0_R: R26.2, U10.2 (IN0)
/WIN_IN1: J10.45 (23 WIN_IN1), R27.1
/WIN_IN1_R: R27.2, U10.5 (IN1)
/WIN_IN2: J10.16 (24 WIN_IN2), R28.1
/WIN_IN2_R: R28.2, U10.9 (IN2)
/WIN_IN3: J10.17 (25 WIN_IN3), R29.1
/WIN_IN3_R: R29.2, U10.10 (IN3)
/WIN_IS: R33.1, U10.7 (IS)
/WIN_PASS_DN: J9.4, U10.13 (OUT3)
/WIN_PASS_UP: J9.3, U10.17 (OUT2)
GND: C1.2, C2.2, C3.2, C5.2, C7.2, C8.2, C9.2, C10.2, C12.2, C13.2, C14.2, C15.2, C16.2, C17.2, C18.2, C19.2, C20.2, C21.2, C22.2, C23.2, C24.2, C25.2, C28.2, C29.2, C30.2, C31.2, C32.2, C33.2, C34.2, C35.2, C36.2, C37.2, C38.2, C39.2, C40.2, C41.2, C42.2, C43.2, C44.2, C45.2, D2.2 (A), D5.2 (A), D6.1 (A), D7.2 (A), D8.2 (A), D9.1 (A), D10.1 (A), D11.1 (A), J1.3, J3.2, J4.2, J4.20, J4.21, J4.23, J5.2, J6.3, J7.3, J8.3, J10.1 (GND), J10.34 (GND), J10.47 (GND), J11.3, J12.2, Q1.2 (S), Q2.2 (S), Q4.2 (E), R2.2, R4.2, R6.2, R8.2, R17.2, R18.2, R19.2, R20.2, R22.2, R24.2, R25.2, R33.2, R34.2, R35.2, R37.2, R39.2, R41.2, R45.2, R47.2, R54.2, R55.2, R56.2, R57.2, R60.2, R61.2, R62.2, R63.2, R65.2, R67.2, R70.2, U1.1 (PGND), U1.6 (AGND), U1.11 (PGND), U2.7 (GND), U2.9 (PAD), U3.2 (GND), U4.2 (GND), U11.3 (PGND1), U11.10 (PGND2), U11.13 (PGND4), U11.20 (PGND3), U11.22 (GND), U11.23 (GND), U11.27 (OCPM), U11.28 (MODE), U11.38 (IN4), U11.45 (PAD), U12.2 (A1), U12.12 (GND), U12.21 (A0), U13.2 (A1), U13.12 (GND), U15.1 (ADDR), U15.3 (GND), U15.5 (AIN1), U15.7 (AIN3), U16.2 (GND), U16.5 (GND)
unnamed: R73.2, R74.1, U17.1 (IN)
unnamed: R75.1, U13.7 (P03), U17.4 (STATUS)
unnamed: TP2.1, U17.3 (OUT), U17.6 (OUT)
PGND: D4.2 (A), J2.6, J2.7, J2.8, R15.2, R16.2, U4.4 (IN-), U17.5 (GND)

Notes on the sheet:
POWER - two supplies that never meet on this board (D-273, D-382)
DP-DCU - DT13-06PA in the enclosure wall (D-362)
SN24 logic 12 V in: SS34 then SMBJ33A, as the ICU (D-273)
SN24 5 V logic buck - the ICU U1 stage copied whole (F13)
DP-DCU-C - comfort connector DT13-08PA (P153, D-382)
SN27 comfort supply in (O15): 5 A Schottky then SMBJ33A to PGND
SN27 servo rail buck, 5 V 5 A - one servo moves at a time (D-379); values confirm vs TI datasheet 8.2
BUS
SN26 CAN2 at 500 kbps - unterminated: the bus ends at the PMU and the dash node (D-346)
INPUTS
SN11 cabin NTC 10k on a local flying lead
SN12 outside-air NTC on DP-DCU 2 - clamp: A on GND, K on +3V3
SN13 comfort-bus current: 2 x 10 mOhm = 5 mOhm, INA180A1 x20 (D-379)
SN18-SN20 panel ribbon: 20-way IDC box header (P157, panel_ribbon) - pin 20 AGND lands on GND here
OUTPUTS
SN16 seat heat driver - the four BTS3011TE STATUS pins (open-drain, latched thermal fault) are wired-OR on SEAT_STATUS to expander U13 P00 through R58 (Y11)
SN16 seat heat passenger
SN16 seat cool driver
SN16 seat cool passenger
SN16 mirror heat: high-side off the comfort supply, out on DP-DCU-B 9 (D-369)
SN22 window commands: quad high-side sourcing 12 V into K5-K8 coils (D-363); fed from logic 12 V
SN17 mirror drive: DRV8962-Q1 on its 44 real pins - 3 half-bridges + channel 4 low FET as the clutch sink, IN4 tied low (D-360); MODE low = 140 ns edges, OCPM low = latch-off (an nSLEEP pulse clears it), VCC tied to DVDD; fed from logic 12 V
SN23 release select: sink K3 / K4 coil during the O10 pulse (D-370)
SN21 wake request: sources 12 V into the PMU wake strip (a diode-OR of 12 V inputs, D-350) - the ICU backlight stage
SN14 blower PWM >= 20 kHz to the final stage at L3-BLW
SN15 servo mode
SN15 servo blend
SN15 servo recirculate
DP-DCU-B - DT13-12PA in the enclosure wall (D-362)
PROCESSOR
Teensy 4.1 - all 42 edge pins used; the bottom pads are not (D-442 settled here)
I/O expander: the slow lines the Teensy has no pins for. RESET low = every port an input = mirror driver asleep
PWR_FLAGs - every rail is driven from off-sheet or through a passive part
WHAT THIS SHEET DOES NOT KNOW (R11)
- Module pin numbers are now the datasheets' (cad/pin_tables.csv, check.py); every footprint is stock KiCad or drawn from the vendor drawing - confirm against the parts in hand (R11).
- The mirror heads: motor and clutch pins, stall current, clutch return (luxury W-332). IPROPI resistor and D-360 wait on it.
- TPS54560B compensation, RT and inductor: proposals from the datasheet method, not checked in WEBENCH.
- DRV8962: charge-pump, DVDD and VCC bypass per TI table 6-1; RIPROPI 1.5k x4 puts ITRIP near 10 A (VREF 3.3 V, 212 uA/A) - confirm vs stall (W-332).
- BTS3011TE STATUS x4 wired-OR to U13 P00 with one 10k pull-up: a latched thermal fault reads low; clearing it needs P00 driven high (3-7 mA per faulted part) with IN low - confirm the expander's drive.
- The wake strip input level: drawn as a 12 V high-side source into a diode-OR strip (D-350); SN21 still confirm.

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
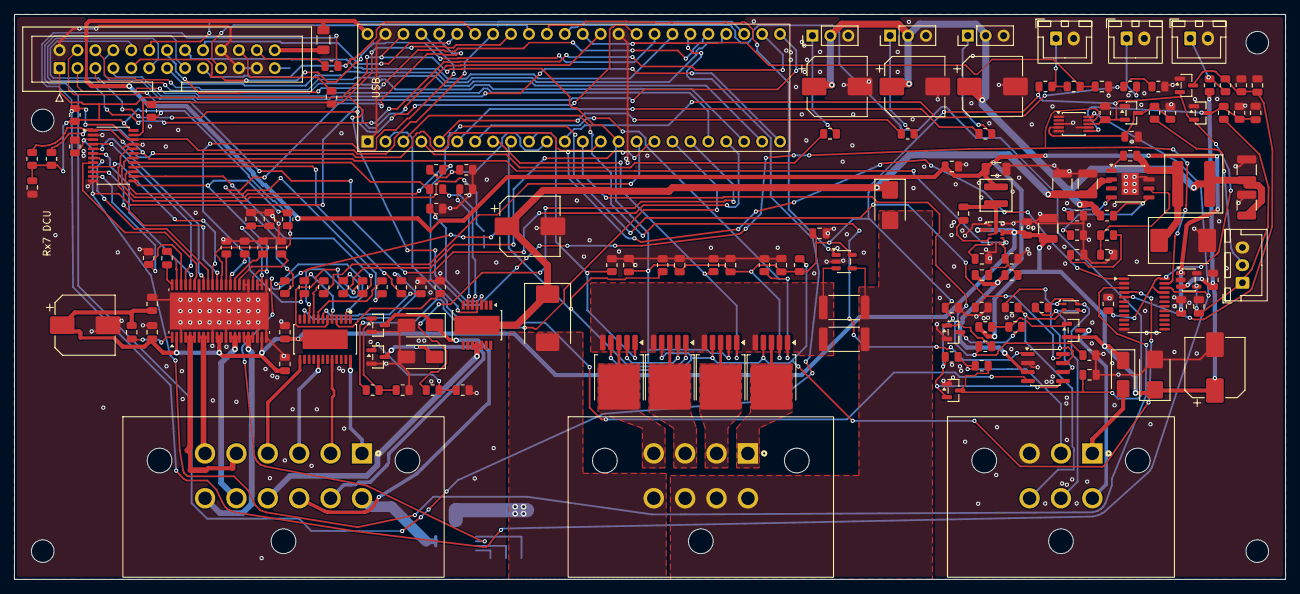
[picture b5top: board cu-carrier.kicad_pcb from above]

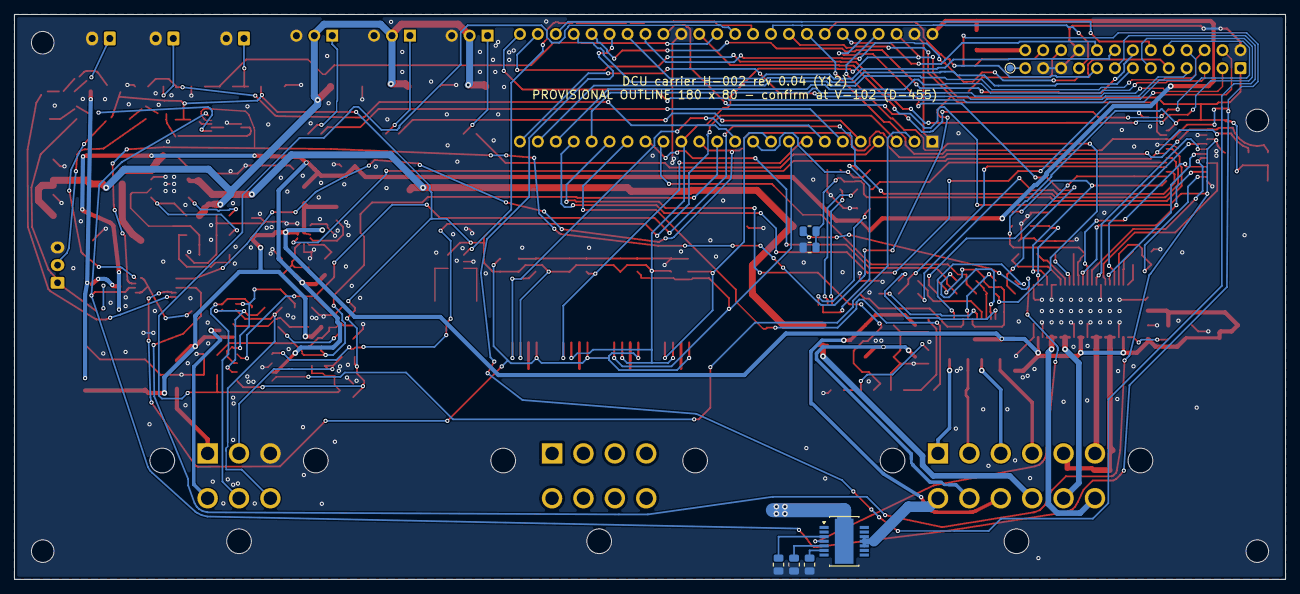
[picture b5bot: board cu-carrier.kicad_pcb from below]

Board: 2 copper layers, 180.0 x 80.0 mm, 169 parts (7 on the bottom side), 146 nets.

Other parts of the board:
H1, H2, H3, H4: M3; MountingHole_3.2mm_M3

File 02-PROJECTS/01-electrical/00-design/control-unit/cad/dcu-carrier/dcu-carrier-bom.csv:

"Ref","Value","Footprint","Qty","DNP"
"C1,C8,C29","68u 63V","Capacitor_SMD:CP_Elec_8x10","3",""
"C2,C9,C10","4.7u 100V X7R","Capacitor_SMD:C_1210_3225Metric","3",""
"C3","220n 100V","Capacitor_SMD:C_0805_2012Metric","1",""
"C4,C11","100n 16V","Capacitor_SMD:C_0805_2012Metric","2",""
"C5","1u 16V","Capacitor_SMD:C_0805_2012Metric","1",""
"C6","20p C0G","Capacitor_SMD:C_0805_2012Metric","1",""
"C7","22u 16V X7R","Capacitor_SMD:C_1206_3216Metric","1",""
"C12","4.7n  confirm","Capacitor_SMD:C_0805_2012Metric","1",""
"C13","47p  confirm","Capacitor_SMD:C_0805_2012Metric","1",""
"C14,C15","47u 10V X7R","Capacitor_SMD:C_1210_3225Metric","2",""
"C16-C24,C34","100n","Capacitor_SMD:C_0805_2012Metric","10",""
"C25,C27,C30","100n 100V","Capacitor_SMD:C_0805_2012Metric","3",""
"C26","1u 25V  confirm","Capacitor_SMD:C_0805_2012Metric","1",""
"C28","1u","Capacitor_SMD:C_0805_2012Metric","1",""
"C31-C33","470u 16V","Capacitor_SMD:CP_Elec_8x10","3",""
"C35","100n  at pin 25 (VCC)","Capacitor_SMD:C_0805_2012Metric","1",""
"C36","10n 100V  VM-PGND1 (TI 6-1)","Capacitor_SMD:C_0805_2012Metric","1",""
"C37","10n 100V  VM-PGND3 (TI 6-1)","Capacitor_SMD:C_0805_2012Metric","1",""
"C38","100n  U13 VCC","Capacitor_SMD:C_0805_2012Metric","1",""
"C39","100n  U15 VDD","Capacitor_SMD:C_0805_2012Metric","1","DNP"
"C40","1u 50V","Capacitor_SMD:C_0805_2012Metric","1","DNP"
"C41,C43-C45","100n","Capacitor_SMD:C_0805_2012Metric","4","DNP"
"C42","2.2u","Capacitor_SMD:C_0805_2012Metric","1","DNP"
"D1","SL310A","Diode_SMD:D_SMA","1",""
"D2,D4","SMBJ33A","Diode_SMD:D_SMB","2",""
"D3","B560C 60V 5A - confirm","Diode_SMD:D_SMC","1",""
"D5","B560C 60V 5A catch","Diode_SMD:D_SMC","1",""
"D6","BAT54S","Package_TO_SOT_SMD:SOT-23","1",""
"D7,D8","SMAJ40A  confirm","Diode_SMD:D_SMA","2",""
"D9-D11","BAT54S","Package_TO_SOT_SMD:SOT-23","3","DNP"
"F1","PTC 0.5A hold 1206 - confirm","Fuse:Fuse_1206_3216Metric","1",""
"J1","DP-DCU  DT13-06PA","dcu-carrier:DT13-06PA","1",""
"J2","DP-DCU-C  DT13-08PA","dcu-carrier:DT13-08PA","1",""
"J3","cabin NTC lead","Connector_JST:JST_XH_B2B-XH-A_1x02_P2.50mm_Vertical","1",""
"J4","panel ribbon 2x13 IDC, keyed","Connector_IDC:IDC-Header_2x13_P2.54mm_Vertical","1",""
"J5","blower pigtail","Connector_JST:JST_XH_B2B-XH-A_1x02_P2.50mm_Vertical","1",""
"J6-J8","servo header","Connector_PinHeader_2.54mm:PinHeader_1x03_P2.54mm_Vertical","3",""
"J9","DP-DCU-B  DT13-12PA","dcu-carrier:DT13-12PA","1",""
"J10","Teensy 4.1 socket - 2 x 24 female headers","dcu-carrier:Teensy41_Socket","1",""
"J11","A/C pressure transducer lead - PLACEHOLDER","Connector_JST:JST_XH_B3B-XH-A_1x03_P2.50mm_Vertical","1","DNP"
"J12","radar alert lead - PLACEHOLDER","Connector_JST:JST_XH_B2B-XH-A_1x02_P2.50mm_Vertical","1","DNP"
"L1","2.2u XAL4020-222","Inductor_SMD:L_Coilcraft_XAL4020-XXX","1",""
"L2","6.8u  Isat >= 7 A - confirm","Inductor_SMD:L_Coilcraft_XAL7030-682","1",""
"L3","common-mode choke - DNP, fit only with R instead removed","Inductor_SMD:L_CommonModeChoke_Coilank_ACM2012","1","DNP"
"Q1,Q2","SQ2364EES","Package_TO_SOT_SMD:SOT-23","2",""
"Q3","SQ2361ES","Package_TO_SOT_SMD:SOT-23","1",""
"Q4","MMBT5551","Package_TO_SOT_SMD:SOT-23","1",""
"R1","100k 1%","Resistor_SMD:R_0805_2012Metric","1",""
"R2","24.9k 1%","Resistor_SMD:R_0805_2012Metric","1",""
"R3,R45","100k","Resistor_SMD:R_0805_2012Metric","2",""
"R4","243k 1%  ~400 kHz","Resistor_SMD:R_0805_2012Metric","1",""
"R5","52.3k 1%","Resistor_SMD:R_0805_2012Metric","1",""
"R6,R11,R13","10k 1%","Resistor_SMD:R_0805_2012Metric","3",""
"R7","16.9k  confirm","Resistor_SMD:R_0805_2012Metric","1",""
"R8,R12,R14,R36,R39,R41,R42,R44,R53","10k","Resistor_SMD:R_0805_2012Metric","9",""
"R9,R10","0R  fitted in place of the choke","Resistor_SMD:R_0805_2012Metric","2",""
"R15,R16","10m 2512 3W","Resistor_SMD:R_2512_6332Metric","2",""
"R17-R20,R22","10k  off at reset","Resistor_SMD:R_0805_2012Metric","5",""
"R21,R23,R26-R32,R51,R52","4.7k","Resistor_SMD:R_0805_2012Metric","11",""
"R24","1.2k  IS unread - no ADC pin left","Resistor_SMD:R_0805_2012Metric","1",""
"R25,R34","47R  PROFET ground","Resistor_SMD:R_0805_2012Metric","2",""
"R33","1.2k  IS unread","Resistor_SMD:R_0805_2012Metric","1",""
"R35","100k  asleep at reset","Resistor_SMD:R_0805_2012Metric","1",""
"R37,R55-R57","1.5k  confirm vs stall (W-332)","Resistor_SMD:R_0805_2012Metric","4",""
"R38,R40,R46,R71,R72","100R","Resistor_SMD:R_0805_2012Metric","5",""
"R43","18k","Resistor_SMD:R_0805_2012Metric","1",""
"R47","10k  off through a reset","Resistor_SMD:R_0805_2012Metric","1",""
"R48-R50","330R","Resistor_SMD:R_0805_2012Metric","3",""
"R54","10k  held in reset until the firmware lets go","Resistor_SMD:R_0805_2012Metric","1",""
"R58","10k  STATUS pull-up (BTS3011TE p.40)","Resistor_SMD:R_0805_2012Metric","1",""
"R59","4.7k","Resistor_SMD:R_0805_2012Metric","1","DNP"
"R60","10k  off at reset","Resistor_SMD:R_0805_2012Metric","1","DNP"
"R61","4.7k  DEN low","Resistor_SMD:R_0805_2012Metric","1","DNP"
"R62","1.2k  IS unread","Resistor_SMD:R_0805_2012Metric","1","DNP"
"R63","47R  PROFET ground","Resistor_SMD:R_0805_2012Metric","1","DNP"
"R64,R66,R68","10k","Resistor_SMD:R_0805_2012Metric","3","DNP"
"R65,R67","20k","Resistor_SMD:R_0805_2012Metric","2","DNP"
"R69","47k","Resistor_SMD:R_0805_2012Metric","1","DNP"
"R70","22k","Resistor_SMD:R_0805_2012Metric","1","DNP"
"U1","LMR36015FSCQ-Q1","Package_DFN_QFN:Texas_RNX0012C_VQFN-14-11-1EP_2x3mm_P0.5mm_EP0.25x1.825mm","1",""
"U2","TPS54560B-Q1","Package_SO:HSOP-8-1EP_3.9x4.9mm_P1.27mm_EP2.41x3.1mm","1",""
"U3","TCAN1042HVDRQ1","Package_SO:SOIC-8_3.9x4.9mm_P1.27mm","1",""
"U4","INA180A1","Package_TO_SOT_SMD:SOT-23-5","1",""
"U5-U8","BTS3011TE","Package_TO_SOT_SMD:TO-252-5_TabPin6","4",""
"U9","BTT6050-1ERA","dcu-carrier:Infineon_PG-TSDSO-14-22","1",""
"U10","BTT6200-4ESA","dcu-carrier:Infineon_PG-TSDSO-24-21","1",""
"U11","DRV8962-Q1","Package_SO:HTSSOP-44-1EP_6.1x14mm_P0.635mm_EP5.2x14mm_Mask4.31x8.26mm","1",""
"U12,U13","TCA9539-Q1","Package_SO:TSSOP-24_4.4x7.8mm_P0.65mm","2",""
"U14","BTT6050-1ERA","dcu-carrier:Infineon_PG-TSDSO-14-22","1","DNP"
"U15","ADS1115-Q1","Package_SO:MSOP-10_3x3mm_P0.5mm","1","DNP"
"U16","TPS7B4250-Q1","Package_TO_SOT_SMD:SOT-23-5","1","DNP"
